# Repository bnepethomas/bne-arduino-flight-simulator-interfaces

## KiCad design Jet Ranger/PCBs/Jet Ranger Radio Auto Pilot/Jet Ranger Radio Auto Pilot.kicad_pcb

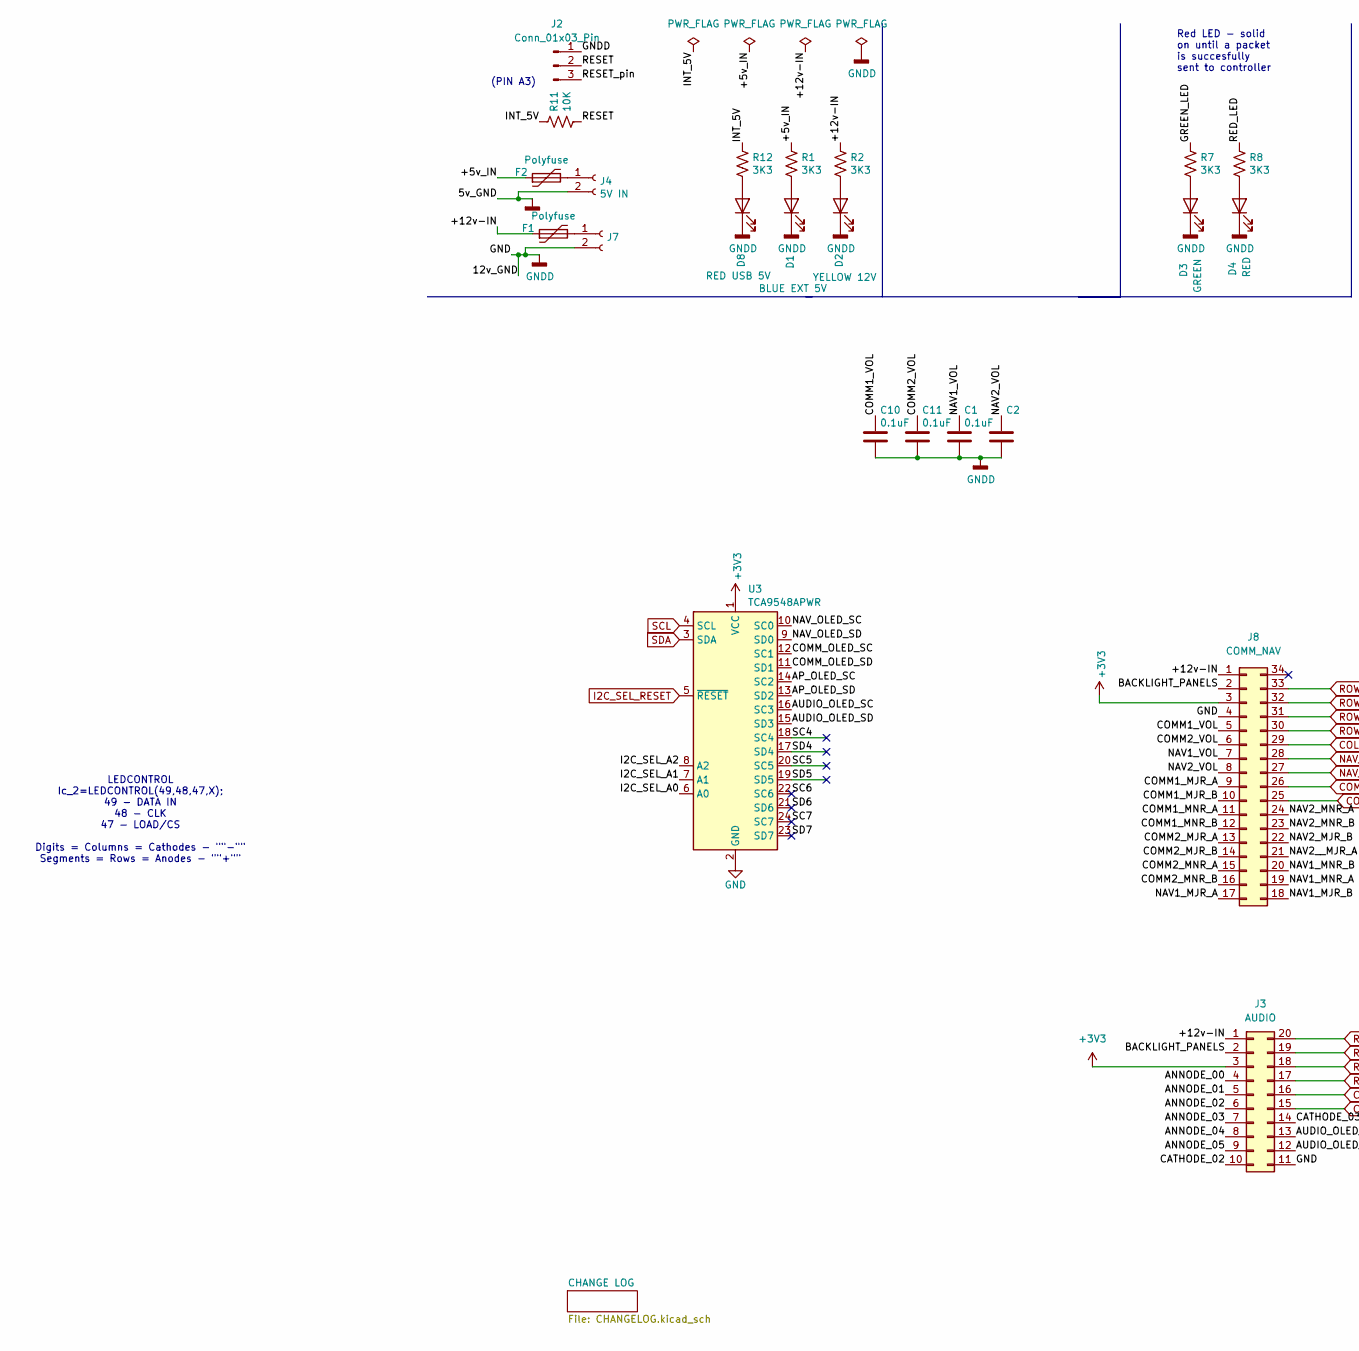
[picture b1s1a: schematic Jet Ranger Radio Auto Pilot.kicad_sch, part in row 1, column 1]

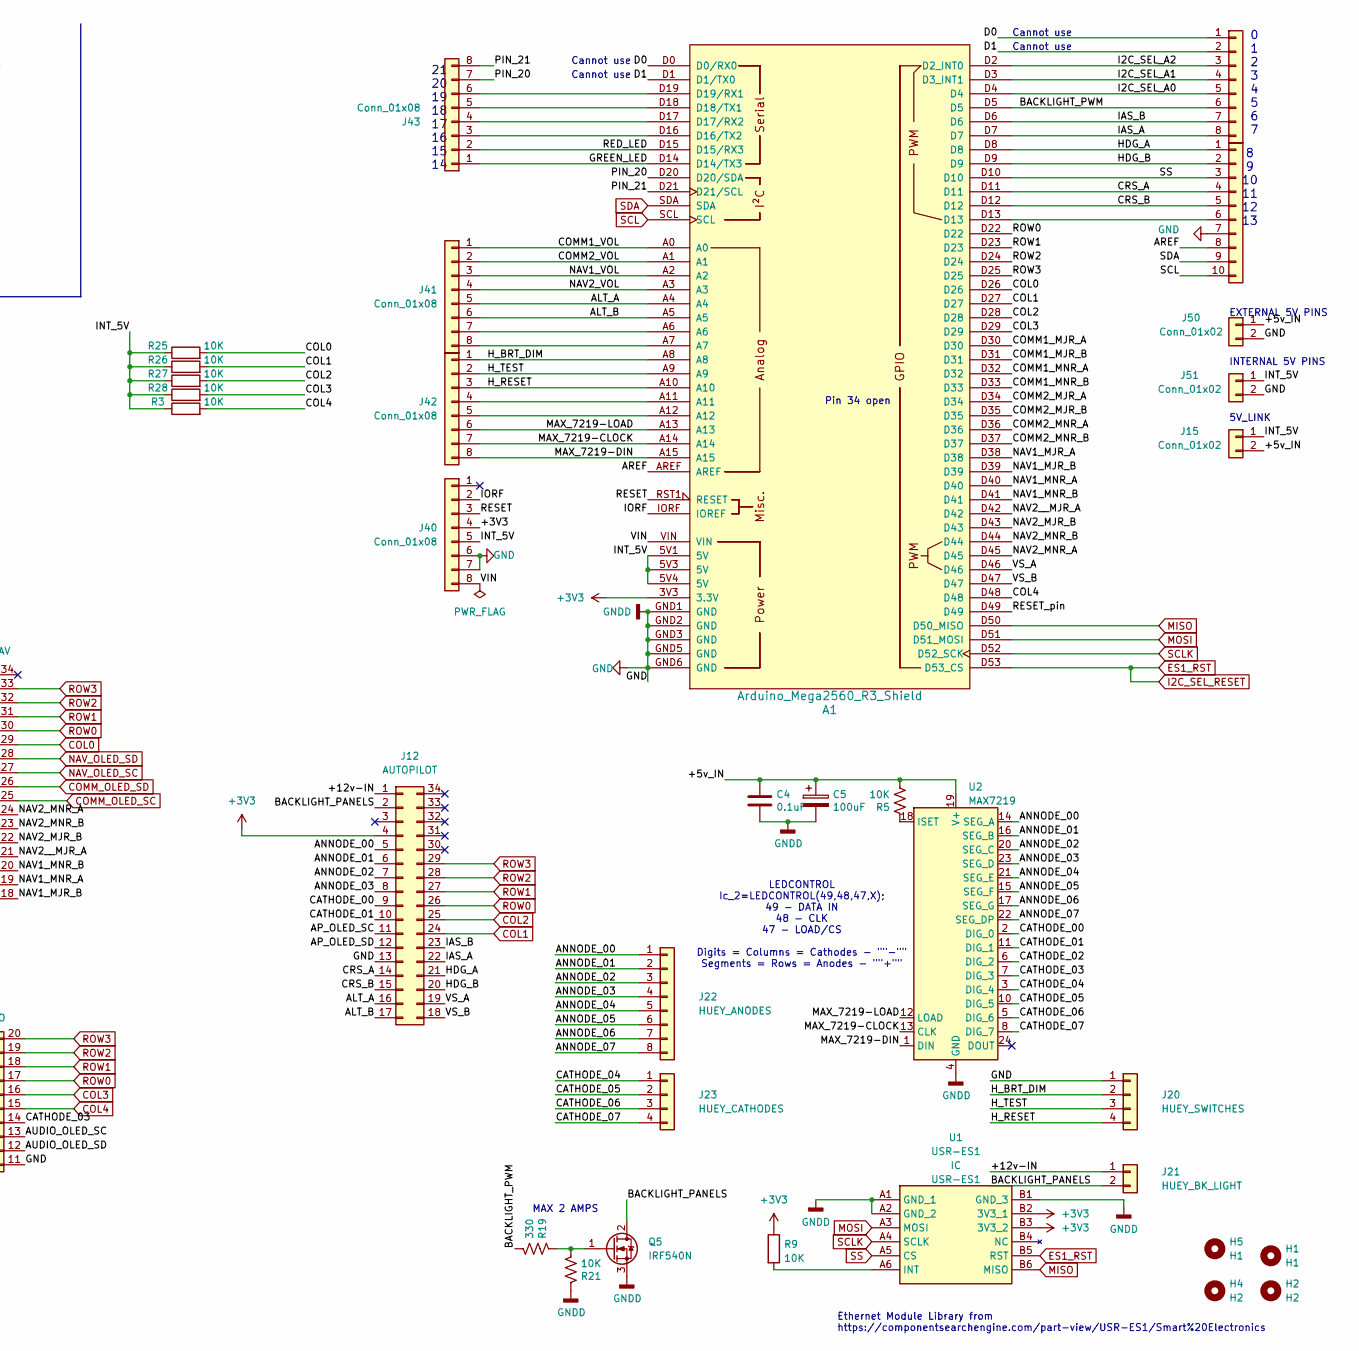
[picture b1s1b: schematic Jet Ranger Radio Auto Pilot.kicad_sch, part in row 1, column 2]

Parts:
A1: Arduino_Mega2560_R3_Shield
C1, C2, C4, C10, C11: 0.1uF; C_Disc_D3.0mm_W2.0mm_P2.50mm
C5: 100uF; C_Radial_D8.0mm_H7.0mm_P3.50mm
D1: BLUE EXT 5V; LED_D3.0mm
D2: YELLOW 12V; LED_D3.0mm
D3: GREEN; LED_D3.0mm
D4: RED; LED_D3.0mm
D8: RED USB 5V; LED_D3.0mm
F1, F2: Polyfuse; Fuse_Littelfuse_395Series
H1, H5: H1; MountingHole_3.2mm_M3
H2, H4: H2; MountingHole_3.2mm_M3
J2: Conn_01x03_Pin; PinHeader_1x03_P2.54mm_Vertical
J3: AUDIO; IDC-Header_2x10_P2.54mm_Vertical
J4: 5V IN; BarrelJack_Horizontal
J7: STEPPER IN 12-20VDC; BarrelJack_Horizontal
J8: COMM_NAV; IDC-Header_2x17_P2.54mm_Vertical
J12: AUTOPILOT; IDC-Header_2x17_P2.54mm_Vertical
J15, J50, J51: Conn_01x02; PinHeader_1x02_P2.54mm_Vertical
J20: HUEY_SWITCHES; Molex_KK-254_AE-6410-04A_1x04_P2.54mm_Vertical
J21: HUEY_BK_LIGHT; Molex_KK-254_AE-6410-02A_1x02_P2.54mm_Vertical
J22: HUEY_ANODES; Molex_KK-254_AE-6410-08A_1x08_P2.54mm_Vertical
J23: HUEY_CATHODES; Molex_KK-254_AE-6410-04A_1x04_P2.54mm_Vertical
J40, J41, J42, J43, J44: Conn_01x08; PinHeader_1x08_P2.54mm_Vertical
J45: Conn_01x10; PinHeader_1x10_P2.54mm_Vertical
Q5: IRF540N; TO-220-3_Vertical
R1, R2, R7, R8, R12: 3K3; R_Axial_DIN0207_L6.3mm_D2.5mm_P2.54mm_Vertical
R3, R5, R9, R11, R21, R25, R26, R27, R28: 10K; R_Axial_DIN0207_L6.3mm_D2.5mm_P2.54mm_Vertical
R19: 330; R_Axial_DIN0207_L6.3mm_D2.5mm_P2.54mm_Vertical
U1: USR-ES1; USRES1; Manufacturer_Part_Number USR-ES1
U2: MAX7219; DIP-24_W7.62mm_LongPads
U3: TCA9548APWR; AllieExpress_TCA9548A

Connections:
+3V3: A1.3V3 (3.3V), J3.3, J8.3, J12.4, J40.4, R9.1, U1.B2 (3V3_1), U1.B3 (3V3_2), U3.1 (VCC)
/+5v_IN: C4.1, C5.1, F2.1, J15.2, J50.1, R1.1, R5.2, U2.19 (V+)
/+12v-IN: F1.1, J3.1, J8.1, J12.1, J21.1, R2.1
/ALT_A: A1.A4, J12.16, J41.5
/ALT_B: A1.A5, J12.17, J41.6
/ANNODE_00: J3.4, J12.5, J22.1, U2.14 (SEG_A)
/ANNODE_01: J3.5, J12.6, J22.2, U2.16 (SEG_B)
/ANNODE_02: J3.6, J12.7, J22.3, U2.20 (SEG_C)
/ANNODE_03: J3.7, J12.8, J22.4, U2.23 (SEG_D)
/ANNODE_04: J3.8, J22.5, U2.21 (SEG_E)
/ANNODE_05: J3.9, J22.6, U2.15 (SEG_F)
/ANNODE_06: J22.7, U2.17 (SEG_G)
/ANNODE_07: J22.8, U2.22 (SEG_DP)
/AP_OLED_SC: J12.11, U3.14 (SC2)
/AP_OLED_SD: J12.12, U3.13 (SD2)
/AREF: A1.AREF, J45.8
/AUDIO_OLED_SC: J3.13, U3.16 (SC3)
/AUDIO_OLED_SD: J3.12, U3.15 (SD3)
/BACKLIGHT_PANELS: J3.2, J8.2, J12.2, J21.2, Q5.2 (D)
/BACKLIGHT_PWM: A1.D5, J44.6, R19.2
/CATHODE_00: J12.9, U2.2 (DIG_0)
/CATHODE_01: J12.10, U2.11 (DIG_1)
/CATHODE_02: J3.10, U2.6 (DIG_2)
/CATHODE_03: J3.14, U2.7 (DIG_3)
/CATHODE_04: J23.1, U2.3 (DIG_4)
/CATHODE_05: J23.2, U2.10 (DIG_5)
/CATHODE_06: J23.3, U2.5 (DIG_6)
/CATHODE_07: J23.4, U2.8 (DIG_7)
/COMM1_MJR_A: A1.D30, J8.9
/COMM1_MJR_B: A1.D31, J8.10
/COMM1_MNR_A: A1.D32, J8.11
/COMM1_MNR_B: A1.D33, J8.12
/COMM1_VOL: A1.A0, C10.1, J8.5, J41.1
/COMM2_MJR_A: A1.D34, J8.13
/COMM2_MJR_B: A1.D35, J8.14
/COMM2_MNR_A: A1.D36, J8.15
/COMM2_MNR_B: A1.D37, J8.16
/COMM2_VOL: A1.A1, C11.1, J8.6, J41.2
/CRS_A: A1.D11, J12.14, J45.4
/CRS_B: A1.D12, J12.15, J45.5
/D0: A1.D0 (D0/RX0), J44.1
/D1: A1.D1 (D1/TX0), J44.2
/GREEN_LED: A1.D14 (D14/TX3), J43.1, R7.1
/HDG_A: A1.D8, J12.21, J45.1
/HDG_B: A1.D9, J12.20, J45.2
/H_BRT_DIM: A1.A8, J20.2, J42.1
/H_RESET: A1.A10, J20.4, J42.3
/H_TEST: A1.A9, J20.3, J42.2
/I2C_SEL_A0: A1.D4, J44.5, U3.6 (A0)
/I2C_SEL_A1: A1.D3 (D3_INT1), J44.4, U3.7 (A1)
/I2C_SEL_A2: A1.D2 (D2_INT0), J44.3, U3.8 (A2)
/IAS_A: A1.D7, J12.22, J44.8
/IAS_B: A1.D6, J12.23, J44.7
/INT_5V: A1.5V1 (5V), A1.5V3 (5V), A1.5V4 (5V), J15.1, J40.5, J51.1, R3.1, R11.1, R12.1, R25.1, R26.1, R27.1, R28.1
/IORF: A1.IORF (IOREF), J40.2
/MAX_7219-CLOCK: A1.A14, J42.7, U2.13 (CLK)
/MAX_7219-DIN: A1.A15, J42.8, U2.1 (DIN)
/MAX_7219-LOAD: A1.A13, J42.6, U2.12 (LOAD)
/NAV1_MJR_A: A1.D38, J8.17
/NAV1_MJR_B: A1.D39, J8.18
/NAV1_MNR_A: A1.D40, J8.19
/NAV1_MNR_B: A1.D41, J8.20
/NAV1_VOL: A1.A2, C1.1, J8.7, J41.3
/NAV2_MJR_B: A1.D43, J8.22
/NAV2_MNR_A: A1.D45, J8.24
/NAV2_MNR_B: A1.D44, J8.23
/NAV2_VOL: A1.A3, C2.1, J8.8, J41.4
/NAV2__MJR_A: A1.D42, J8.21
/PIN_20: A1.D20 (D20/SDA), J43.7
/PIN_21: A1.D21 (D21/SCL), J43.8
/RED_LED: A1.D15 (D15/RX3), J43.2, R8.1
/RESET: A1.RST1 (RESET), J2.2, J40.3, R11.2
/RESET_pin: A1.D49, J2.3
/SC4: U3.18 (SC4)
/SC5: U3.20 (SC5)
/SC6: U3.22 (SC6)
/SC7: U3.24 (SC7)
/SD4: U3.17 (SD4)
/SD5: U3.19 (SD5)
/SD6: U3.21 (SD6)
/SD7: U3.23 (SD7)
/VIN: A1.VIN, J40.8
/VS_A: A1.D46, J12.19
/VS_B: A1.D47, J12.18
COL0: A1.D26, J8.29, R25.2
COL1: A1.D27, J12.24, R26.2
COL2: A1.D28, J12.25, R27.2
COL3: A1.D29, J3.16, R28.2
COL4: A1.D48, J3.15, R3.2
COMM_OLED_SC: J8.25, U3.12 (SC1)
COMM_OLED_SD: J8.26, U3.11 (SD1)
ES1_RST: A1.D53 (D53_CS), U1.B5 (RST), U3.5 (~RESET)
GND: A1.GND1 (GND), A1.GND2 (GND), A1.GND3 (GND), A1.GND5 (GND), A1.GND6 (GND), C1.2, C2.2, C4.2, C5.2, C10.2, C11.2, D1.1 (K), D2.1 (K), D3.1 (K), D4.1 (K), D8.1 (K), J2.1, J3.11, J4.2, J7.2, J8.4, J12.13, J20.1, J40.6, J40.7, J45.7, J50.2, J51.2, Q5.3 (S), R21.1, U1.A1 (GND_1), U1.A2 (GND_2), U1.B1 (GND_3), U2.4 (GND), U2.9 (GND), U3.2 (GND)
MISO: A1.D50 (D50_MISO), U1.B6 (MISO)
MOSI: A1.D51 (D51_MOSI), U1.A3 (MOSI)
NAV_OLED_SC: J8.27, U3.10 (SC0)
NAV_OLED_SD: J8.28, U3.9 (SD0)
unnamed: A1.D16 (D16/TX2), J43.3
unnamed: A1.D17 (D17/RX2), J43.4
unnamed: A1.D18 (D18/TX1), J43.5
unnamed: A1.D19 (D19/RX1), J43.6
unnamed: D1.2 (A), R1.2
unnamed: D2.2 (A), R2.2
unnamed: D3.2 (A), R7.2
unnamed: D4.2 (A), R8.2
unnamed: D8.2 (A), R12.2
unnamed: F2.2, J4.1
unnamed: F1.2, J7.1
unnamed: A1.A6, J41.7
unnamed: A1.A7, J41.8
unnamed: A1.A11, J42.4
unnamed: A1.A12, J42.5
unnamed: A1.D13, J45.6
unnamed: Q5.1 (G), R19.1, R21.2
unnamed: R9.2, U1.A6 (INT)
unnamed: R5.1, U2.18 (ISET)
ROW0: A1.D22, J3.17, J8.30, J12.26
ROW1: A1.D23, J3.18, J8.31, J12.27
ROW2: A1.D24, J3.19, J8.32, J12.28
ROW3: A1.D25, J3.20, J8.33, J12.29
SCL: A1.SCL, J45.10, U3.4 (SCL)
SCLK: A1.D52 (D52_SCK), U1.A4 (SCLK)
SDA: A1.SDA, J45.9, U3.3 (SDA)
SS: A1.D10, J45.3, U1.A5 (CS)

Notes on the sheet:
Pin 34 open
MAX 2 AMPS
INTERNAL 5V PINS
Ethernet Module Library from https://componentsearchengine.com/part-view/USR-ES1/Smart%20Electronics
LEDCONTROL Ic_2=LEDCONTROL(49,48,47,X); 49 - DATA IN 48 - CLK 47 - LOAD/CS Digits = Columns = Cathodes - ""-"" Segments = Rows = Anodes - ""+""
Cannot use
(PIN A3)
0 1 2 3 4 5 6 7
Red LED - solid on until a packet is succesfully sent to controller
5V_LINK
21 20 19 18 17 16 15 14
EXTERNAL 5V PINS
8 9 10 11 12 13

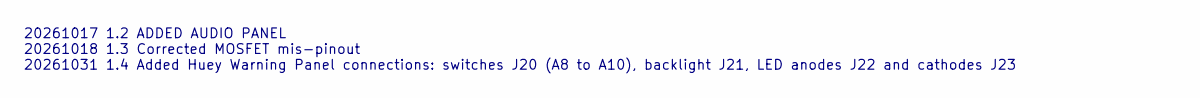
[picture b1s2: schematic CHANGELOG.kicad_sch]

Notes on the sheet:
20261017 1.2 ADDED AUDIO PANEL 20261018 1.3 Corrected MOSFET mis-pinout 20261031 1.4 Added Huey Warning Panel connections: switches J20 (A8 to A10), backlight J21, LED anodes J22 and cathodes J23

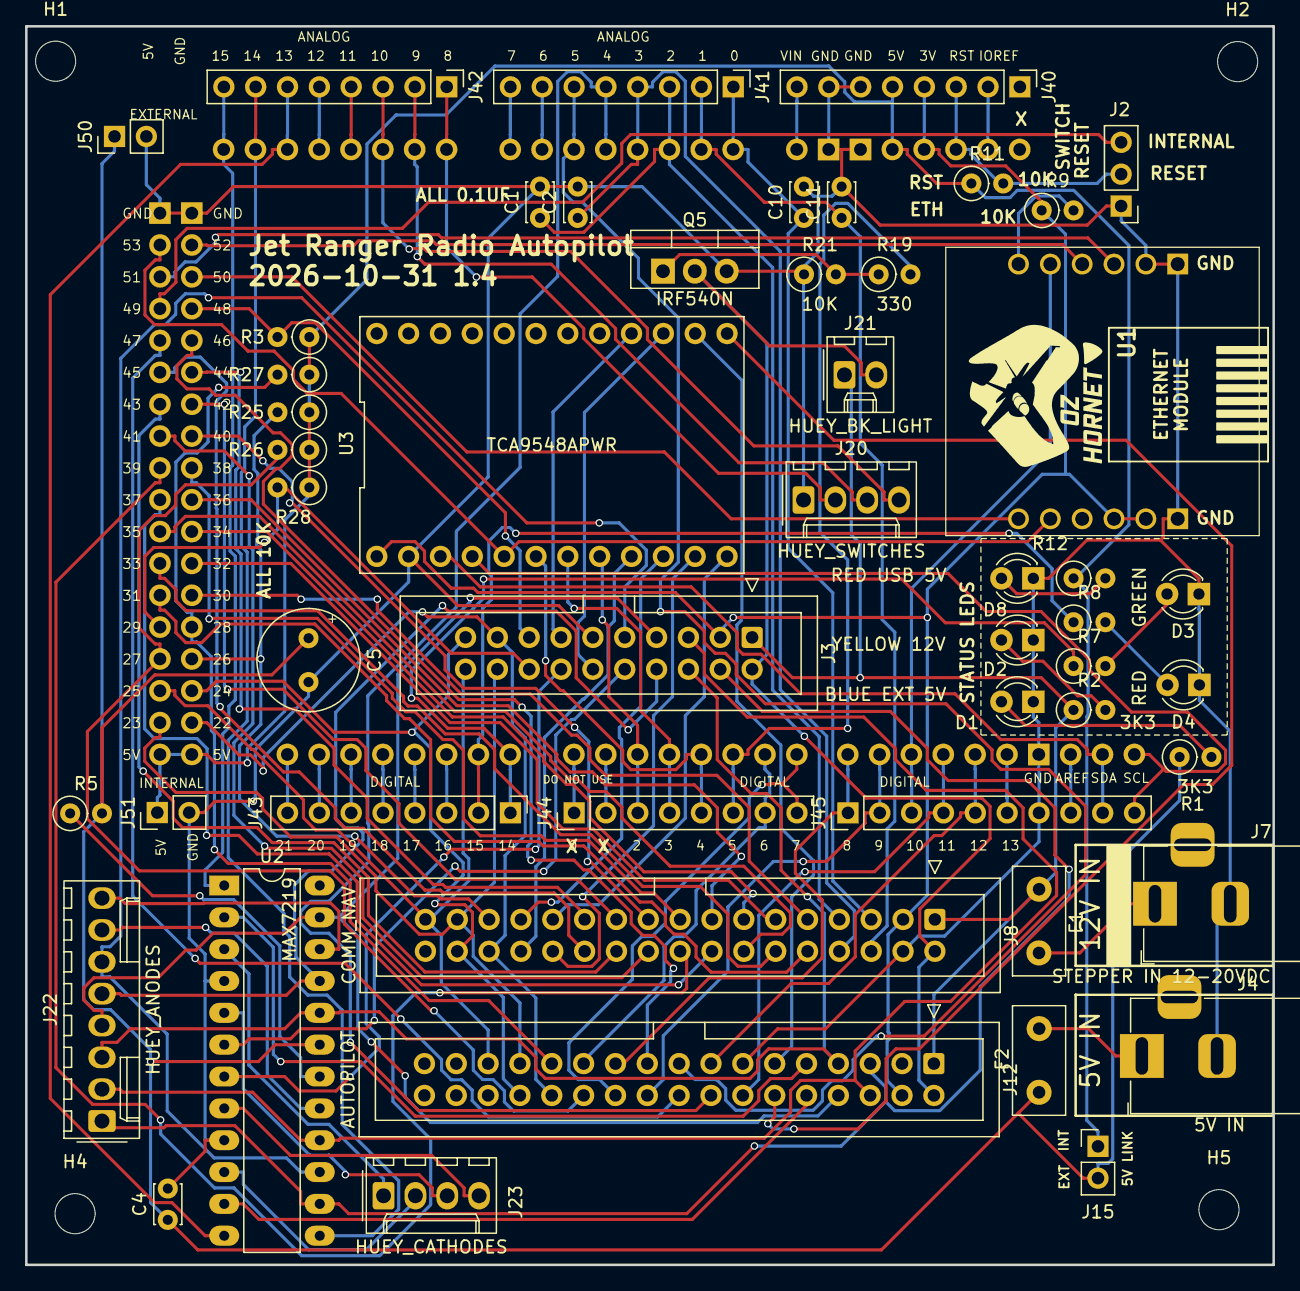
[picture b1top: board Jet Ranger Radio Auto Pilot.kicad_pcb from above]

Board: 2 copper layers, 99.5 x 98.8 mm, 56 parts (0 on the bottom side), 116 nets.

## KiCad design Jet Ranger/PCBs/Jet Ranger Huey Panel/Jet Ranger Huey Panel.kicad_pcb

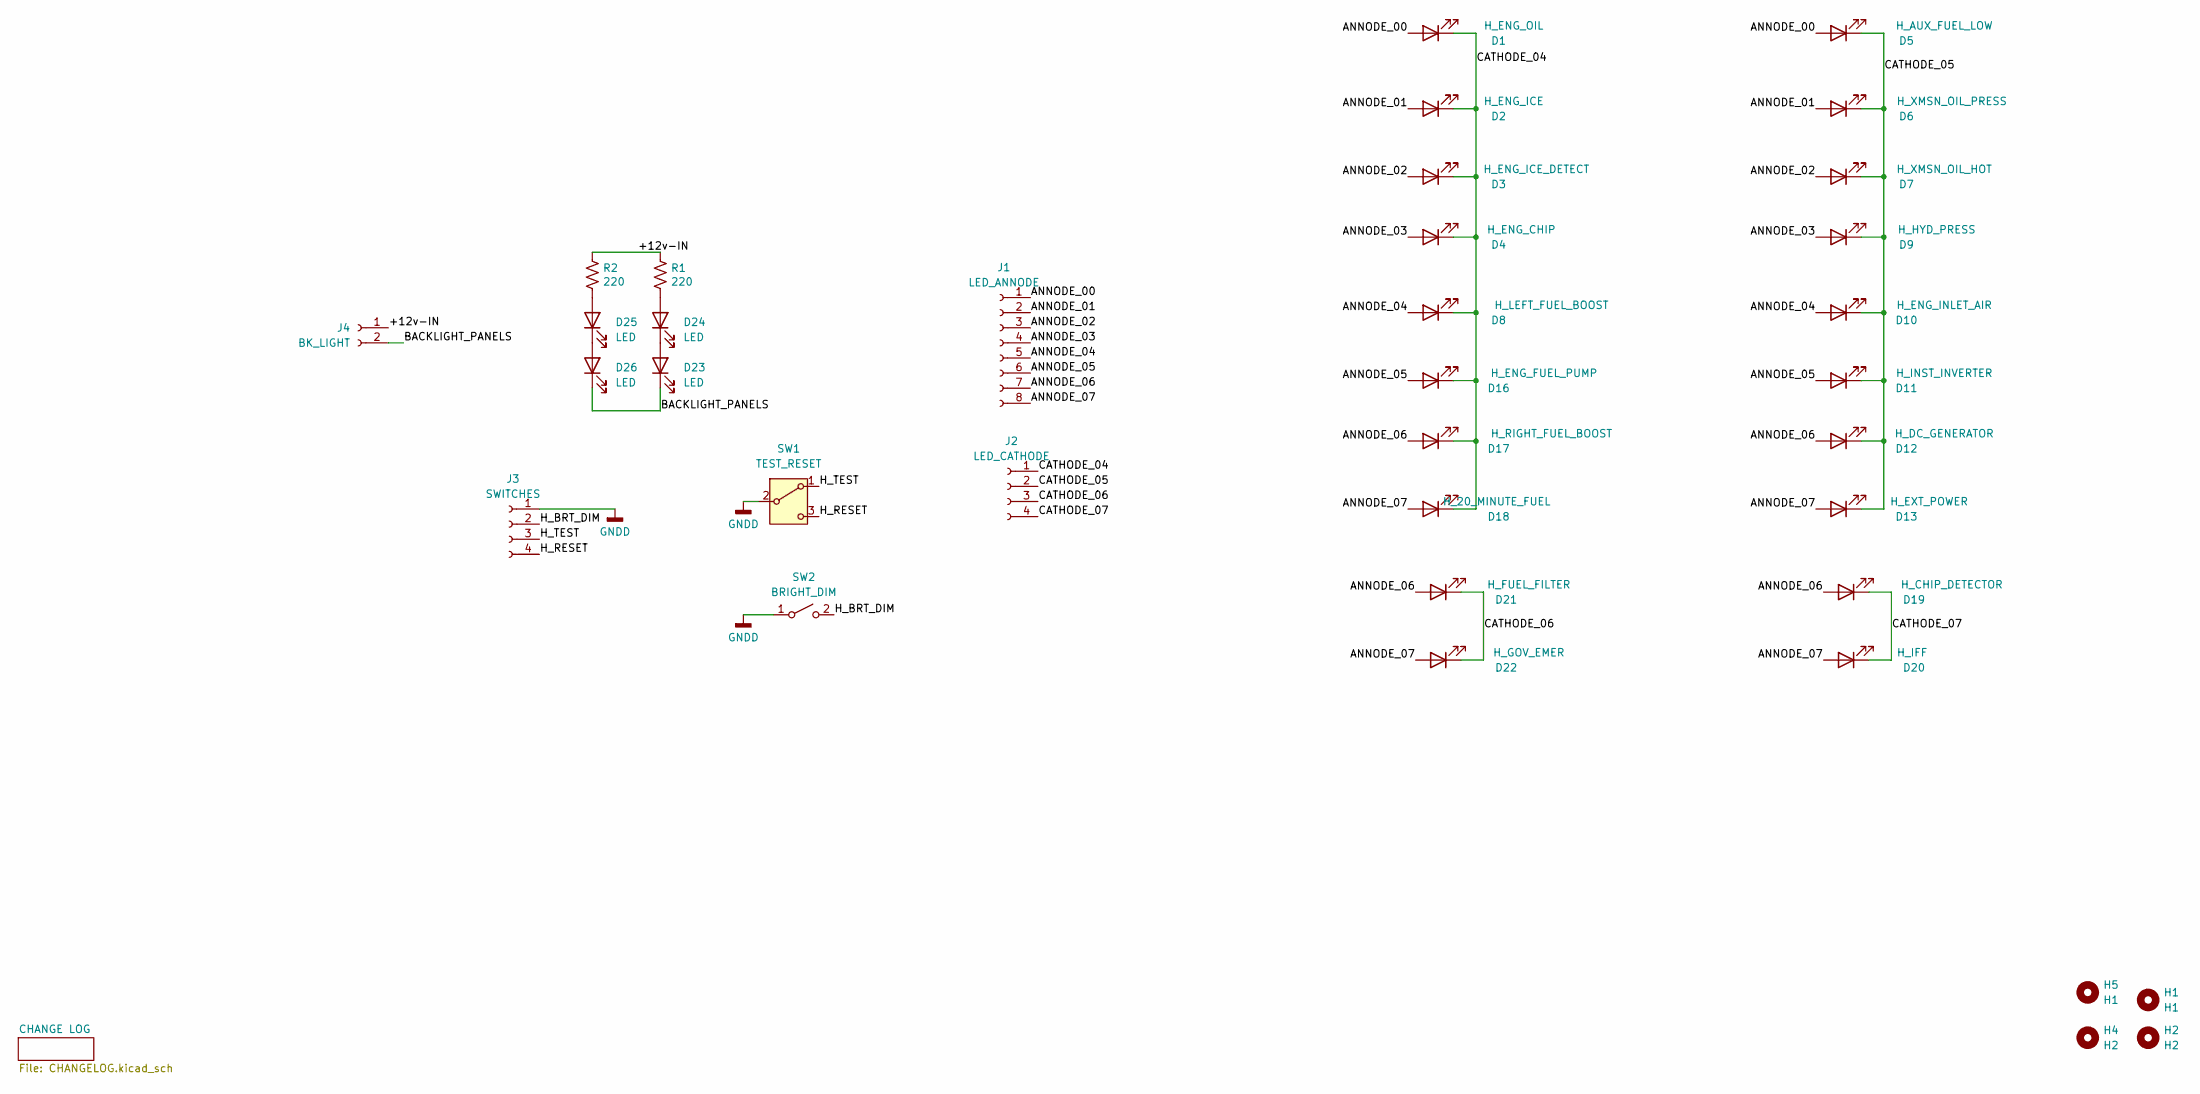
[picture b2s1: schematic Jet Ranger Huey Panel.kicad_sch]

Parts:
D1: H_ENG_OIL; LED_D3.0mm
D2: H_ENG_ICE; LED_D3.0mm
D3: H_ENG_ICE_DETECT; LED_D3.0mm
D4: H_ENG_CHIP; LED_D3.0mm
D5: H_AUX_FUEL_LOW; LED_D3.0mm
D6: H_XMSN_OIL_PRESS; LED_D3.0mm
D7: H_XMSN_OIL_HOT; LED_D3.0mm
D8: H_LEFT_FUEL_BOOST; LED_D3.0mm
D9: H_HYD_PRESS; LED_D3.0mm
D10: H_ENG_INLET_AIR; LED_D3.0mm
D11: H_INST_INVERTER; LED_D3.0mm
D12: H_DC_GENERATOR; LED_D3.0mm
D13: H_EXT_POWER; LED_D3.0mm
D16: H_ENG_FUEL_PUMP; LED_D3.0mm
D17: H_RIGHT_FUEL_BOOST; LED_D3.0mm
D18: H_20_MINUTE_FUEL; LED_D3.0mm
D19: H_CHIP_DETECTOR; LED_D3.0mm
D20: H_IFF; LED_D3.0mm
D21: H_FUEL_FILTER; LED_D3.0mm
D22: H_GOV_EMER; LED_D3.0mm
D23, D24, D25, D26: LED; LED_D3.0mm
H1, H5: H1; MountingHole_3.2mm_M3
H2, H4: H2; MountingHole_3.2mm_M3
J1: LED_ANNODE; Molex_KK-254_AE-6410-08A_1x08_P2.54mm_Vertical
J2: LED_CATHODE; Molex_KK-254_AE-6410-04A_1x04_P2.54mm_Vertical
J3: SWITCHES; Molex_KK-254_AE-6410-04A_1x04_P2.54mm_Vertical
J4: BK_LIGHT; Molex_KK-254_AE-6410-02A_1x02_P2.54mm_Vertical
R1, R2: 220; R_Axial_DIN0207_L6.3mm_D2.5mm_P2.54mm_Vertical
SW1: TEST_RESET; Molex_KK-254_AE-6410-03A_1x03_P2.54mm_Vertical
SW2: BRIGHT_DIM; Molex_KK-254_AE-6410-02A_1x02_P2.54mm_Vertical

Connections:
/+12v-IN: J4.1, R1.1, R2.1
/ANNODE_00: D1.2 (A), D5.2 (A), J1.1
/ANNODE_01: D2.2 (A), D6.2 (A), J1.2
/ANNODE_02: D3.2 (A), D7.2 (A), J1.3
/ANNODE_03: D4.2 (A), D9.2 (A), J1.4
/ANNODE_04: D8.2 (A), D10.2 (A), J1.5
/ANNODE_05: D11.2 (A), D16.2 (A), J1.6
/ANNODE_06: D12.2 (A), D17.2 (A), D19.2 (A), D21.2 (A), J1.7
/ANNODE_07: D13.2 (A), D18.2 (A), D20.2 (A), D22.2 (A), J1.8
/BACKLIGHT_PANELS: D23.1 (K), D26.1 (K), J4.2
/CATHODE_04: D1.1 (K), D2.1 (K), D3.1 (K), D4.1 (K), D8.1 (K), D16.1 (K), D17.1 (K), D18.1 (K), J2.1
/CATHODE_05: D5.1 (K), D6.1 (K), D7.1 (K), D9.1 (K), D10.1 (K), D11.1 (K), D12.1 (K), D13.1 (K), J2.2
/CATHODE_06: D21.1 (K), D22.1 (K), J2.3
/CATHODE_07: D19.1 (K), D20.1 (K), J2.4
/H_BRT_DIM: J3.2, SW2.2 (B)
/H_RESET: J3.4, SW1.3 (C)
/H_TEST: J3.3, SW1.1 (A)
GNDD: J3.1, SW1.2 (B), SW2.1 (A)
unnamed: D23.2 (A), D24.1 (K)
unnamed: D24.2 (A), R1.2
unnamed: D25.2 (A), R2.2
unnamed: D25.1 (K), D26.2 (A)

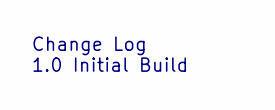
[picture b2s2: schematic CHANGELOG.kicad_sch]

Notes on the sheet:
Change Log 1.0 Initial Build

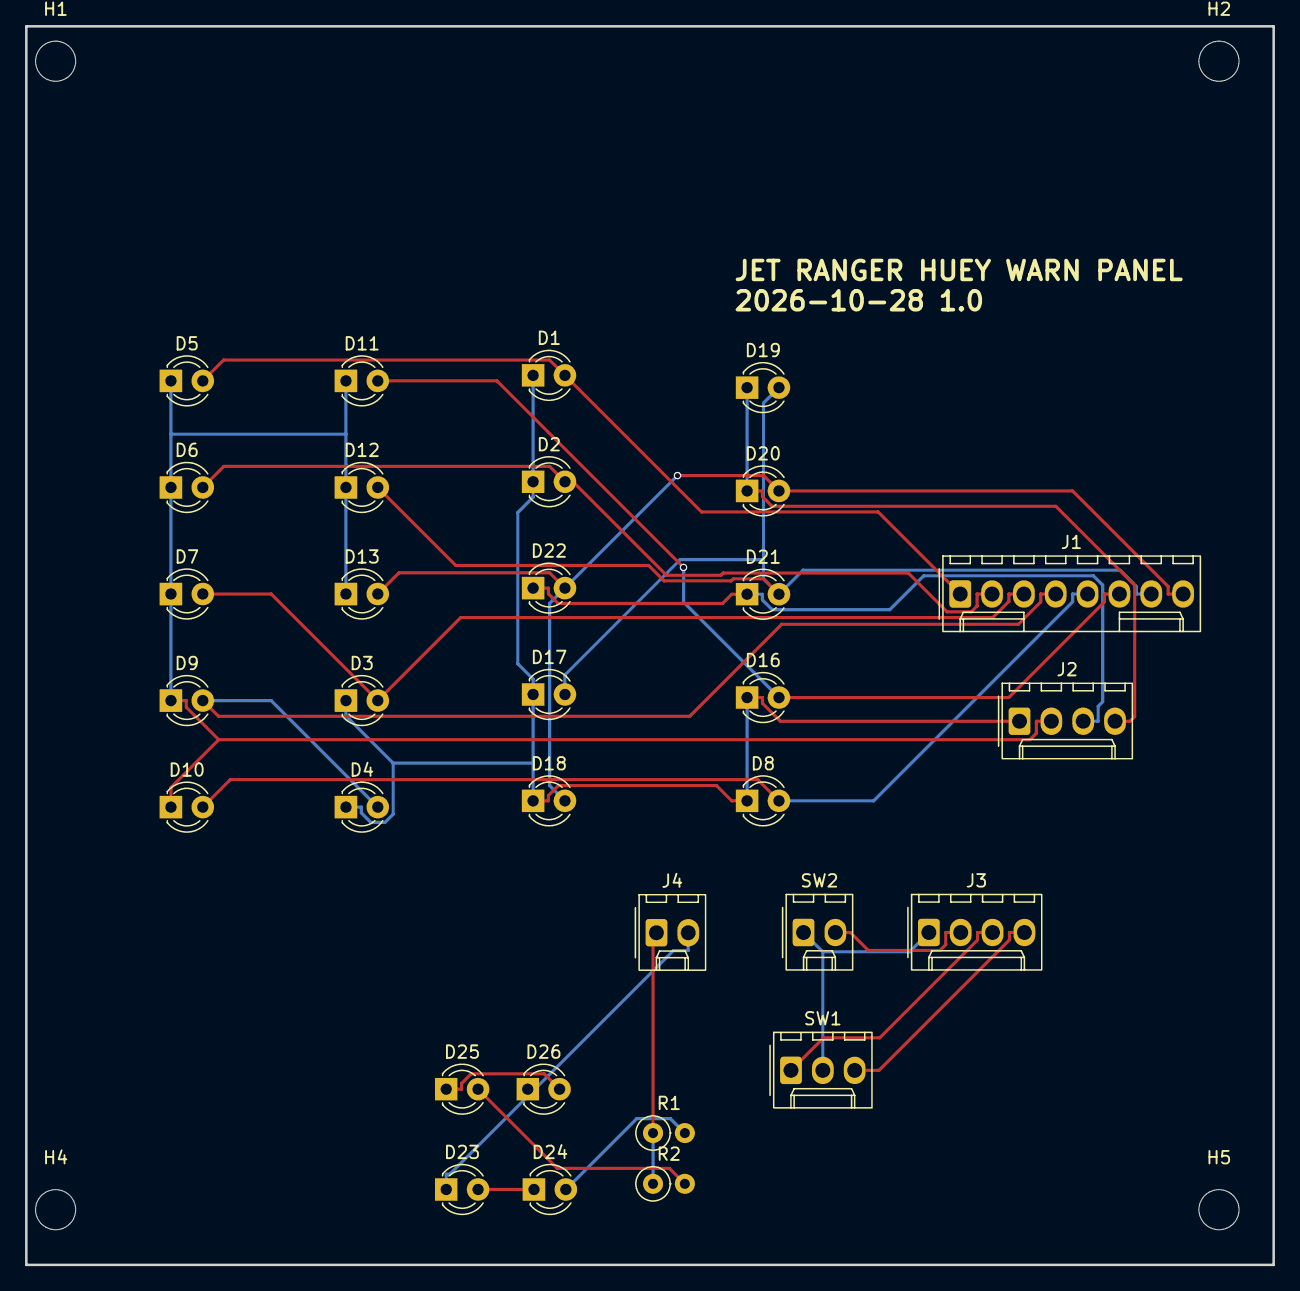
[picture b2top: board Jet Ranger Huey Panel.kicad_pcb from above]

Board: 2 copper layers, 99.5 x 98.8 mm, 36 parts (0 on the bottom side), 22 nets.

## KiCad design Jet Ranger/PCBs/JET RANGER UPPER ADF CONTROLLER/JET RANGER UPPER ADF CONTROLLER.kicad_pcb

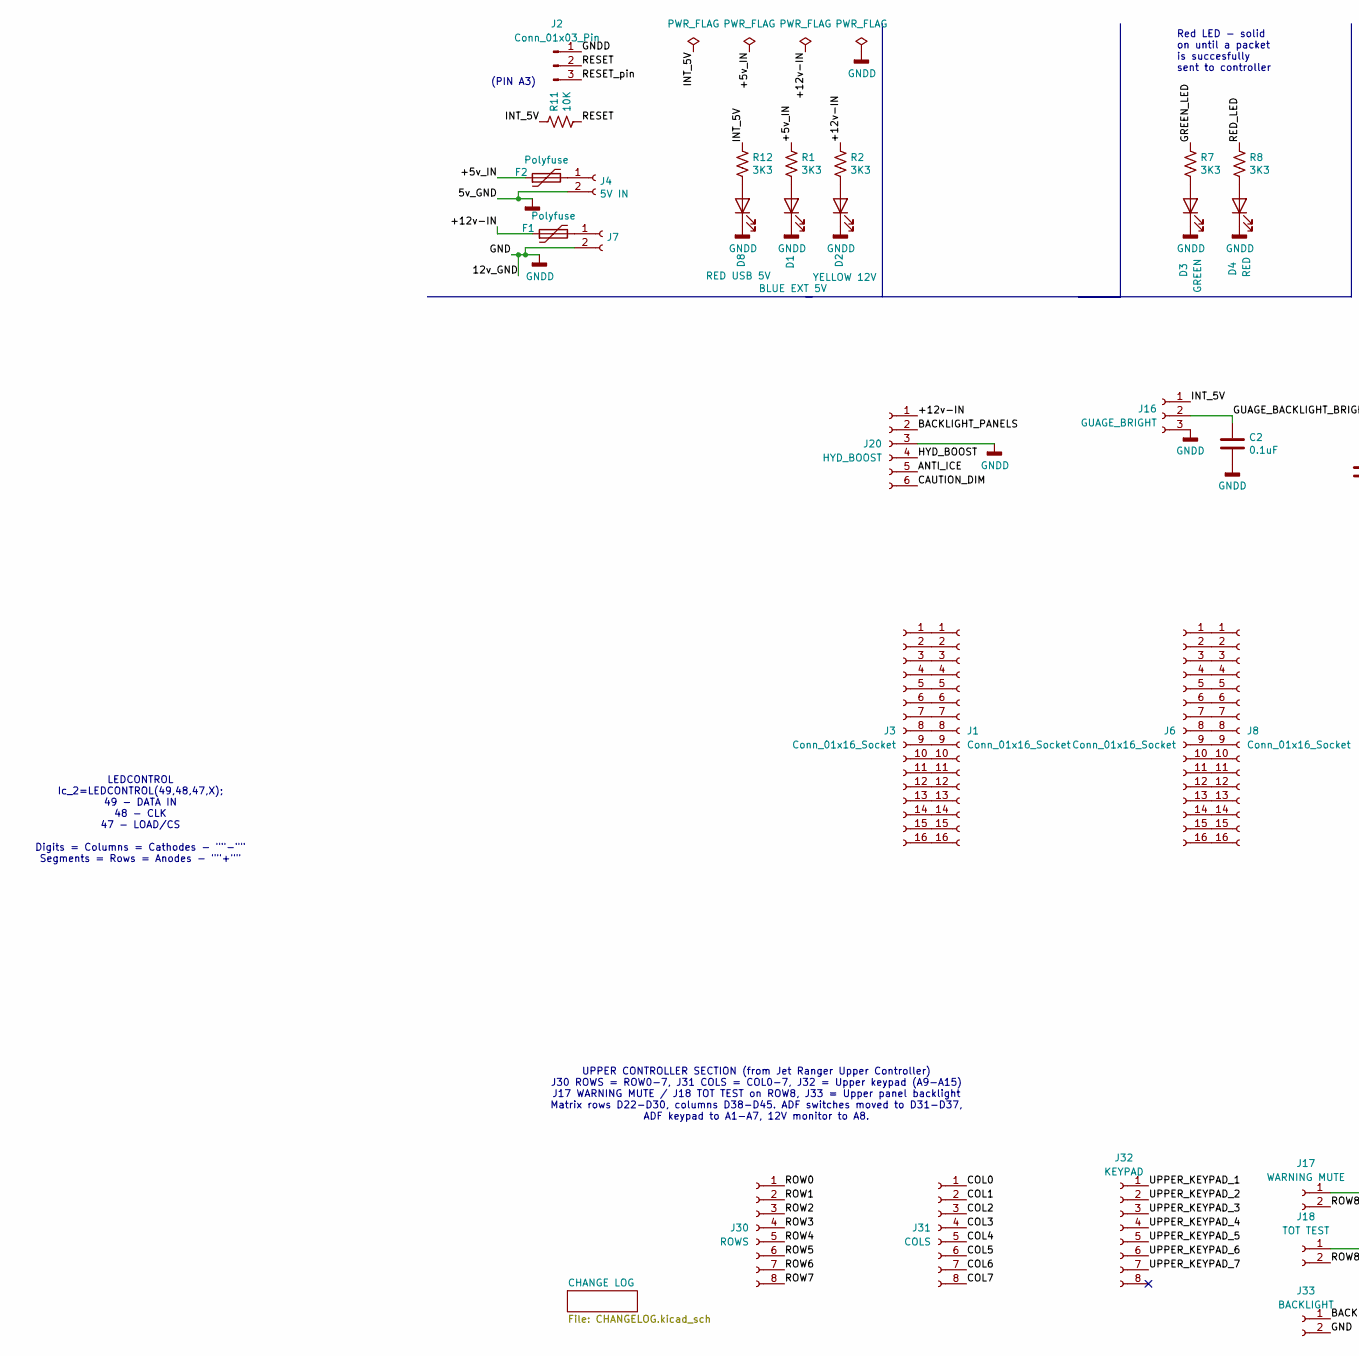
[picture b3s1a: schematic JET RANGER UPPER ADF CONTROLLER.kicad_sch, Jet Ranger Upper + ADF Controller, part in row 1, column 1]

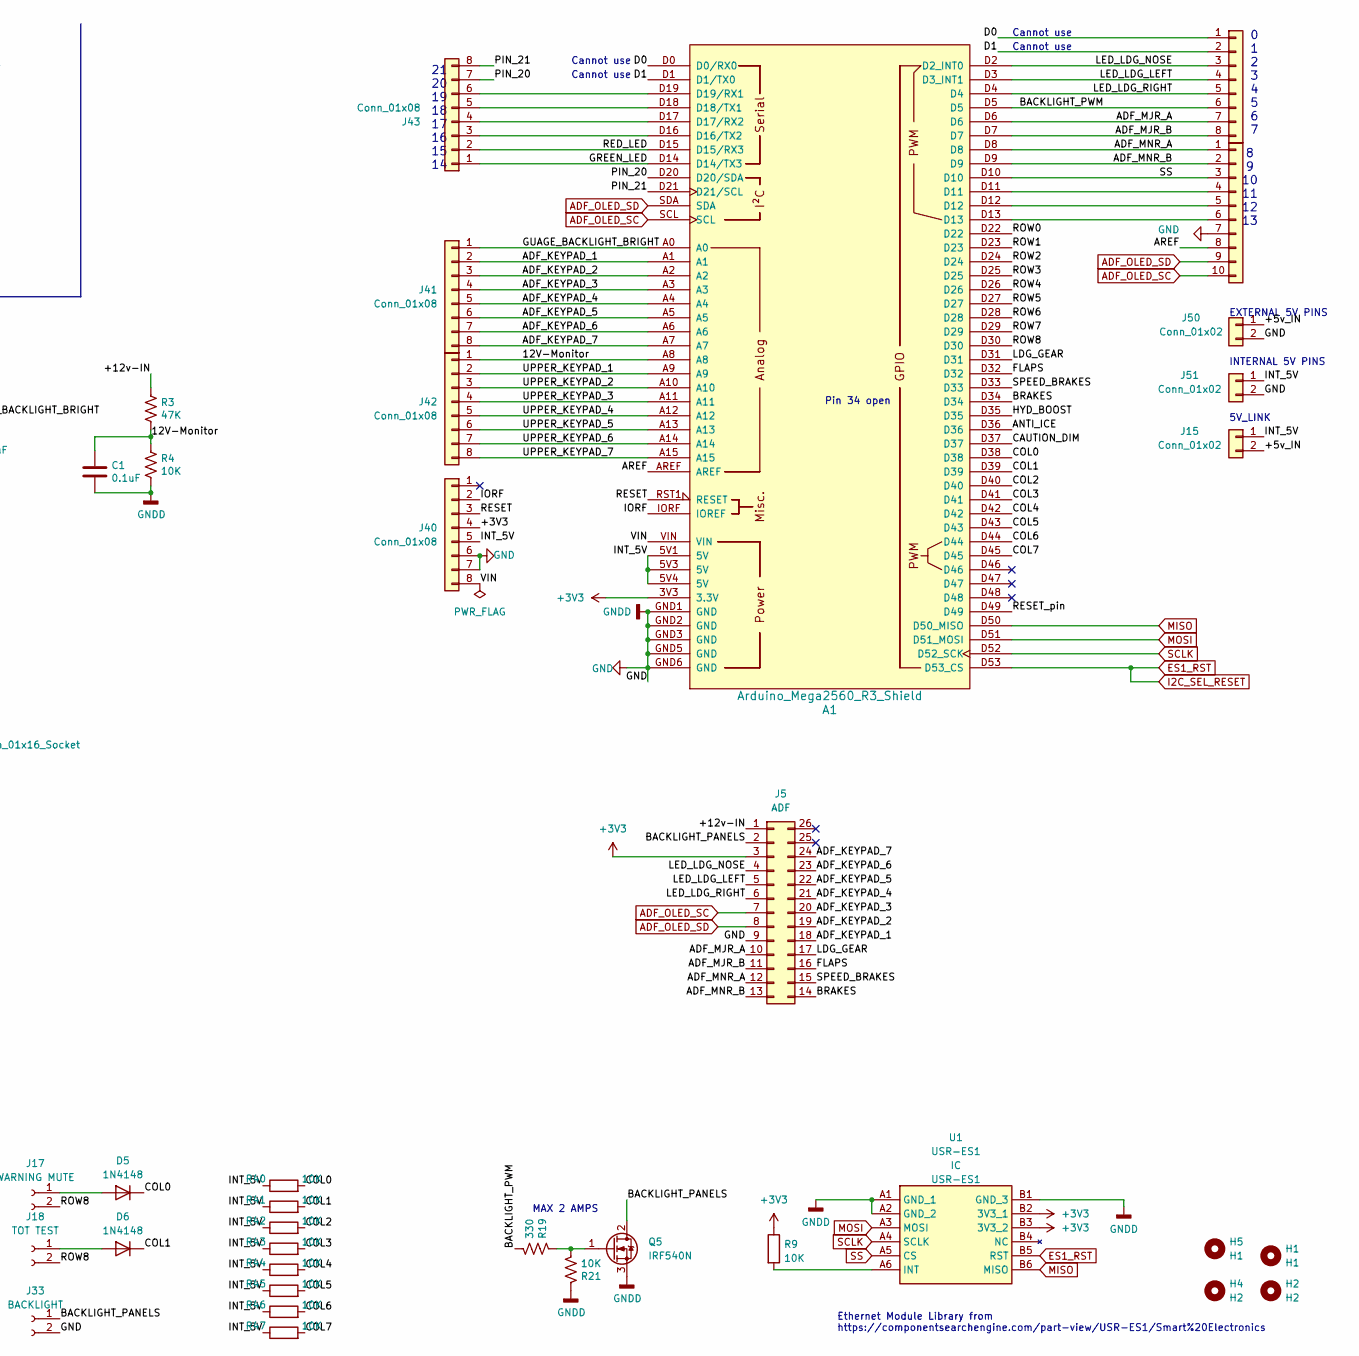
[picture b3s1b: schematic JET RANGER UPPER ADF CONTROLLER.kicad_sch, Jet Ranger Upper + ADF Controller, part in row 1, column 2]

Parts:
A1: Arduino_Mega2560_R3_Shield
C1, C2: 0.1uF; C_Disc_D6.0mm_W2.5mm_P5.00mm
D1: BLUE EXT 5V; LED_D3.0mm
D2: YELLOW 12V; LED_D3.0mm
D3: GREEN; LED_D3.0mm
D4: RED; LED_D3.0mm
D5, D6: 1N4148; D_DO-35_SOD27_P7.62mm_Horizontal
D8: RED USB 5V; LED_D3.0mm
F1, F2: Polyfuse; Fuse_Littelfuse_395Series
H1, H5: H1; MountingHole_3.2mm_M3
H2, H4: H2; MountingHole_3.2mm_M3
J1, J3, J6, J8: Conn_01x16_Socket; PinHeader_1x16_P2.54mm_Vertical
J2: Conn_01x03_Pin; PinHeader_1x03_P2.54mm_Vertical
J4: 5V IN; BarrelJack_Horizontal
J5: ADF; IDC-Header_2x13_P2.54mm_Vertical
J7: STEPPER IN 12-20VDC; BarrelJack_Horizontal
J15, J50, J51: Conn_01x02; PinHeader_1x02_P2.54mm_Vertical
J16: GUAGE_BRIGHT; Molex_KK-254_AE-6410-03A_1x03_P2.54mm_Vertical
J17: WARNING MUTE; Molex_KK-254_AE-6410-02A_1x02_P2.54mm_Vertical
J18: TOT TEST; Molex_KK-254_AE-6410-02A_1x02_P2.54mm_Vertical
J20: HYD_BOOST; Molex_KK-254_AE-6410-06A_1x06_P2.54mm_Vertical
J30: ROWS; Molex_KK-254_AE-6410-08A_1x08_P2.54mm_Vertical
J31: COLS; Molex_KK-254_AE-6410-08A_1x08_P2.54mm_Vertical
J32: KEYPAD; Molex_KK-254_AE-6410-08A_1x08_P2.54mm_Vertical
J33: BACKLIGHT; Molex_KK-254_AE-6410-02A_1x02_P2.54mm_Vertical
J40, J41, J42, J43, J44: Conn_01x08; PinHeader_1x08_P2.54mm_Vertical
J45: Conn_01x10; PinHeader_1x10_P2.54mm_Vertical
Q5: IRF540N; TO-220-3_Vertical
R1, R2, R7, R8, R12: 3K3; R_Axial_DIN0207_L6.3mm_D2.5mm_P2.54mm_Vertical
R3: 47K; R_Axial_DIN0207_L6.3mm_D2.5mm_P2.54mm_Vertical
R4, R9, R11, R21, R40, R41, R42, R43, R44, R45, R46, R47: 10K; R_Axial_DIN0207_L6.3mm_D2.5mm_P2.54mm_Vertical
R19: 330; R_Axial_DIN0207_L6.3mm_D2.5mm_P2.54mm_Vertical
U1: USR-ES1; USRES1; Manufacturer_Part_Number USR-ES1

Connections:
+3V3: A1.3V3 (3.3V), J5.3, J40.4, R9.1, U1.B2 (3V3_1), U1.B3 (3V3_2)
/12V-Monitor: A1.A8, C1.1, J42.1, R3.2, R4.1
/+5v_IN: F2.1, J15.2, J50.1, R1.1
/+12v-IN: F1.1, J5.1, J20.1, R2.1, R3.1
/ADF_KEYPAD_1: A1.A1, J5.18, J41.2
/ADF_KEYPAD_2: A1.A2, J5.19, J41.3
/ADF_KEYPAD_3: A1.A3, J5.20, J41.4
/ADF_KEYPAD_4: A1.A4, J5.21, J41.5
/ADF_KEYPAD_5: A1.A5, J5.22, J41.6
/ADF_KEYPAD_6: A1.A6, J5.23, J41.7
/ADF_KEYPAD_7: A1.A7, J5.24, J41.8
/ADF_MJR_A: A1.D6, J5.10, J44.7
/ADF_MJR_B: A1.D7, J5.11, J44.8
/ADF_MNR_A: A1.D8, J5.12, J45.1
/ADF_MNR_B: A1.D9, J5.13, J45.2
/ANTI_ICE: A1.D36, J20.5
/AREF: A1.AREF, J45.8
/BACKLIGHT_PANELS: J5.2, J20.2, J33.1, Q5.2 (D)
/BACKLIGHT_PWM: A1.D5, J44.6, R19.2
/BRAKES: A1.D34, J5.14
/CAUTION_DIM: A1.D37, J20.6
/COL0: A1.D38, D5.1 (K), J31.1, R40.2
/COL1: A1.D39, D6.1 (K), J31.2, R41.2
/COL2: A1.D40, J31.3, R42.2
/COL3: A1.D41, J31.4, R43.2
/COL4: A1.D42, J31.5, R44.2
/COL5: A1.D43, J31.6, R45.2
/COL6: A1.D44, J31.7, R46.2
/COL7: A1.D45, J31.8, R47.2
/D0: A1.D0 (D0/RX0), J44.1
/D1: A1.D1 (D1/TX0), J44.2
/FLAPS: A1.D32, J5.16
/GREEN_LED: A1.D14 (D14/TX3), J43.1, R7.1
/GUAGE_BACKLIGHT_BRIGHT: A1.A0, C2.1, J16.2, J41.1
/HYD_BOOST: A1.D35, J20.4
/INT_5V: A1.5V1 (5V), A1.5V3 (5V), A1.5V4 (5V), J15.1, J16.1, J40.5, J51.1, R11.1, R12.1, R40.1, R41.1, R42.1, R43.1, R44.1, R45.1, R46.1, R47.1
/IORF: A1.IORF (IOREF), J40.2
/LDG_GEAR: A1.D31, J5.17
/LED_LDG_LEFT: A1.D3 (D3_INT1), J5.5, J44.4
/LED_LDG_NOSE: A1.D2 (D2_INT0), J5.4, J44.3
/LED_LDG_RIGHT: A1.D4, J5.6, J44.5
/PIN_20: A1.D20 (D20/SDA), J43.7
/PIN_21: A1.D21 (D21/SCL), J43.8
/RED_LED: A1.D15 (D15/RX3), J43.2, R8.1
/RESET: A1.RST1 (RESET), J2.2, J40.3, R11.2
/RESET_pin: A1.D49, J2.3
/ROW0: A1.D22, J30.1
/ROW1: A1.D23, J30.2
/ROW2: A1.D24, J30.3
/ROW3: A1.D25, J30.4
/ROW4: A1.D26, J30.5
/ROW5: A1.D27, J30.6
/ROW6: A1.D28, J30.7
/ROW7: A1.D29, J30.8
/ROW8: A1.D30, J17.2, J18.2
/SPEED_BRAKES: A1.D33, J5.15
/UPPER_KEYPAD_1: A1.A9, J32.1, J42.2
/UPPER_KEYPAD_2: A1.A10, J32.2, J42.3
/UPPER_KEYPAD_3: A1.A11, J32.3, J42.4
/UPPER_KEYPAD_4: A1.A12, J32.4, J42.5
/UPPER_KEYPAD_5: A1.A13, J32.5, J42.6
/UPPER_KEYPAD_6: A1.A14, J32.6, J42.7
/UPPER_KEYPAD_7: A1.A15, J32.7, J42.8
/VIN: A1.VIN, J40.8
ADF_OLED_SC: A1.SCL, J5.7, J45.10
ADF_OLED_SD: A1.SDA, J5.8, J45.9
ES1_RST: A1.D53 (D53_CS), U1.B5 (RST)
GND: A1.GND1 (GND), A1.GND2 (GND), A1.GND3 (GND), A1.GND5 (GND), A1.GND6 (GND), C1.2, C2.2, D1.1 (K), D2.1 (K), D3.1 (K), D4.1 (K), D8.1 (K), J2.1, J4.2, J5.9, J7.2, J16.3, J20.3, J33.2, J40.6, J40.7, J45.7, J50.2, J51.2, Q5.3 (S), R4.2, R21.1, U1.A1 (GND_1), U1.A2 (GND_2), U1.B1 (GND_3)
MISO: A1.D50 (D50_MISO), U1.B6 (MISO)
MOSI: A1.D51 (D51_MOSI), U1.A3 (MOSI)
unnamed: A1.D16 (D16/TX2), J43.3
unnamed: A1.D17 (D17/RX2), J43.4
unnamed: A1.D18 (D18/TX1), J43.5
unnamed: A1.D19 (D19/RX1), J43.6
unnamed: D1.2 (A), R1.2
unnamed: D2.2 (A), R2.2
unnamed: D3.2 (A), R7.2
unnamed: D4.2 (A), R8.2
unnamed: D5.2 (A), J17.1
unnamed: D6.2 (A), J18.1
unnamed: D8.2 (A), R12.2
unnamed: J1.1, J3.1
unnamed: J1.2, J3.2
unnamed: J1.3, J3.3
unnamed: J1.4, J3.4
unnamed: J1.5, J3.5
unnamed: J1.6, J3.6
unnamed: J1.7, J3.7
unnamed: J1.8, J3.8
unnamed: J1.9, J3.9
unnamed: J1.10, J3.10
unnamed: J1.11, J3.11
unnamed: J1.12, J3.12
unnamed: J1.13, J3.13
unnamed: J1.14, J3.14
unnamed: J1.15, J3.15
unnamed: J1.16, J3.16
unnamed: F2.2, J4.1
unnamed: J6.1, J8.1
unnamed: J6.2, J8.2
unnamed: J6.3, J8.3
unnamed: J6.4, J8.4
unnamed: J6.5, J8.5
unnamed: J6.6, J8.6
unnamed: J6.7, J8.7
unnamed: J6.8, J8.8
unnamed: J6.9, J8.9
unnamed: J6.10, J8.10
unnamed: J6.11, J8.11
unnamed: J6.12, J8.12
unnamed: J6.13, J8.13
unnamed: J6.14, J8.14
unnamed: J6.15, J8.15
unnamed: J6.16, J8.16
unnamed: F1.2, J7.1
unnamed: A1.D11, J45.4
unnamed: A1.D12, J45.5
unnamed: A1.D13, J45.6
unnamed: Q5.1 (G), R19.1, R21.2
unnamed: R9.2, U1.A6 (INT)
SCLK: A1.D52 (D52_SCK), U1.A4 (SCLK)
SS: A1.D10, J45.3, U1.A5 (CS)

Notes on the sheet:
Pin 34 open
MAX 2 AMPS
INTERNAL 5V PINS
Ethernet Module Library from https://componentsearchengine.com/part-view/USR-ES1/Smart%20Electronics
Cannot use
(PIN A3)
0 1 2 3 4 5 6 7
LEDCONTROL Ic_2=LEDCONTROL(49,48,47,X); 49 - DATA IN 48 - CLK 47 - LOAD/CS Digits = Columns = Cathodes - ""-"" Segments = Rows = Anodes - ""+""
Red LED - solid on until a packet is succesfully sent to controller
5V_LINK
21 20 19 18 17 16 15 14
EXTERNAL 5V PINS
8 9 10 11 12 13
UPPER CONTROLLER SECTION (from Jet Ranger Upper Controller) J30 ROWS = ROW0-7, J31 COLS = COL0-7, J32 = Upper keypad (A9-A15) J17 WARNING MUTE / J18 TOT TEST on ROW8, J33 = Upper panel backlight Matrix rows D22-D30, columns D38-D45. ADF switches moved to D31-D37, ADF keypad to A1-A7, 12V monitor to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

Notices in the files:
Jet Ranger/PCBs/Jet Ranger 13 Stepper/Jet Ranger 13 Stepper.kicad_pcb:
© OZ HORNET
